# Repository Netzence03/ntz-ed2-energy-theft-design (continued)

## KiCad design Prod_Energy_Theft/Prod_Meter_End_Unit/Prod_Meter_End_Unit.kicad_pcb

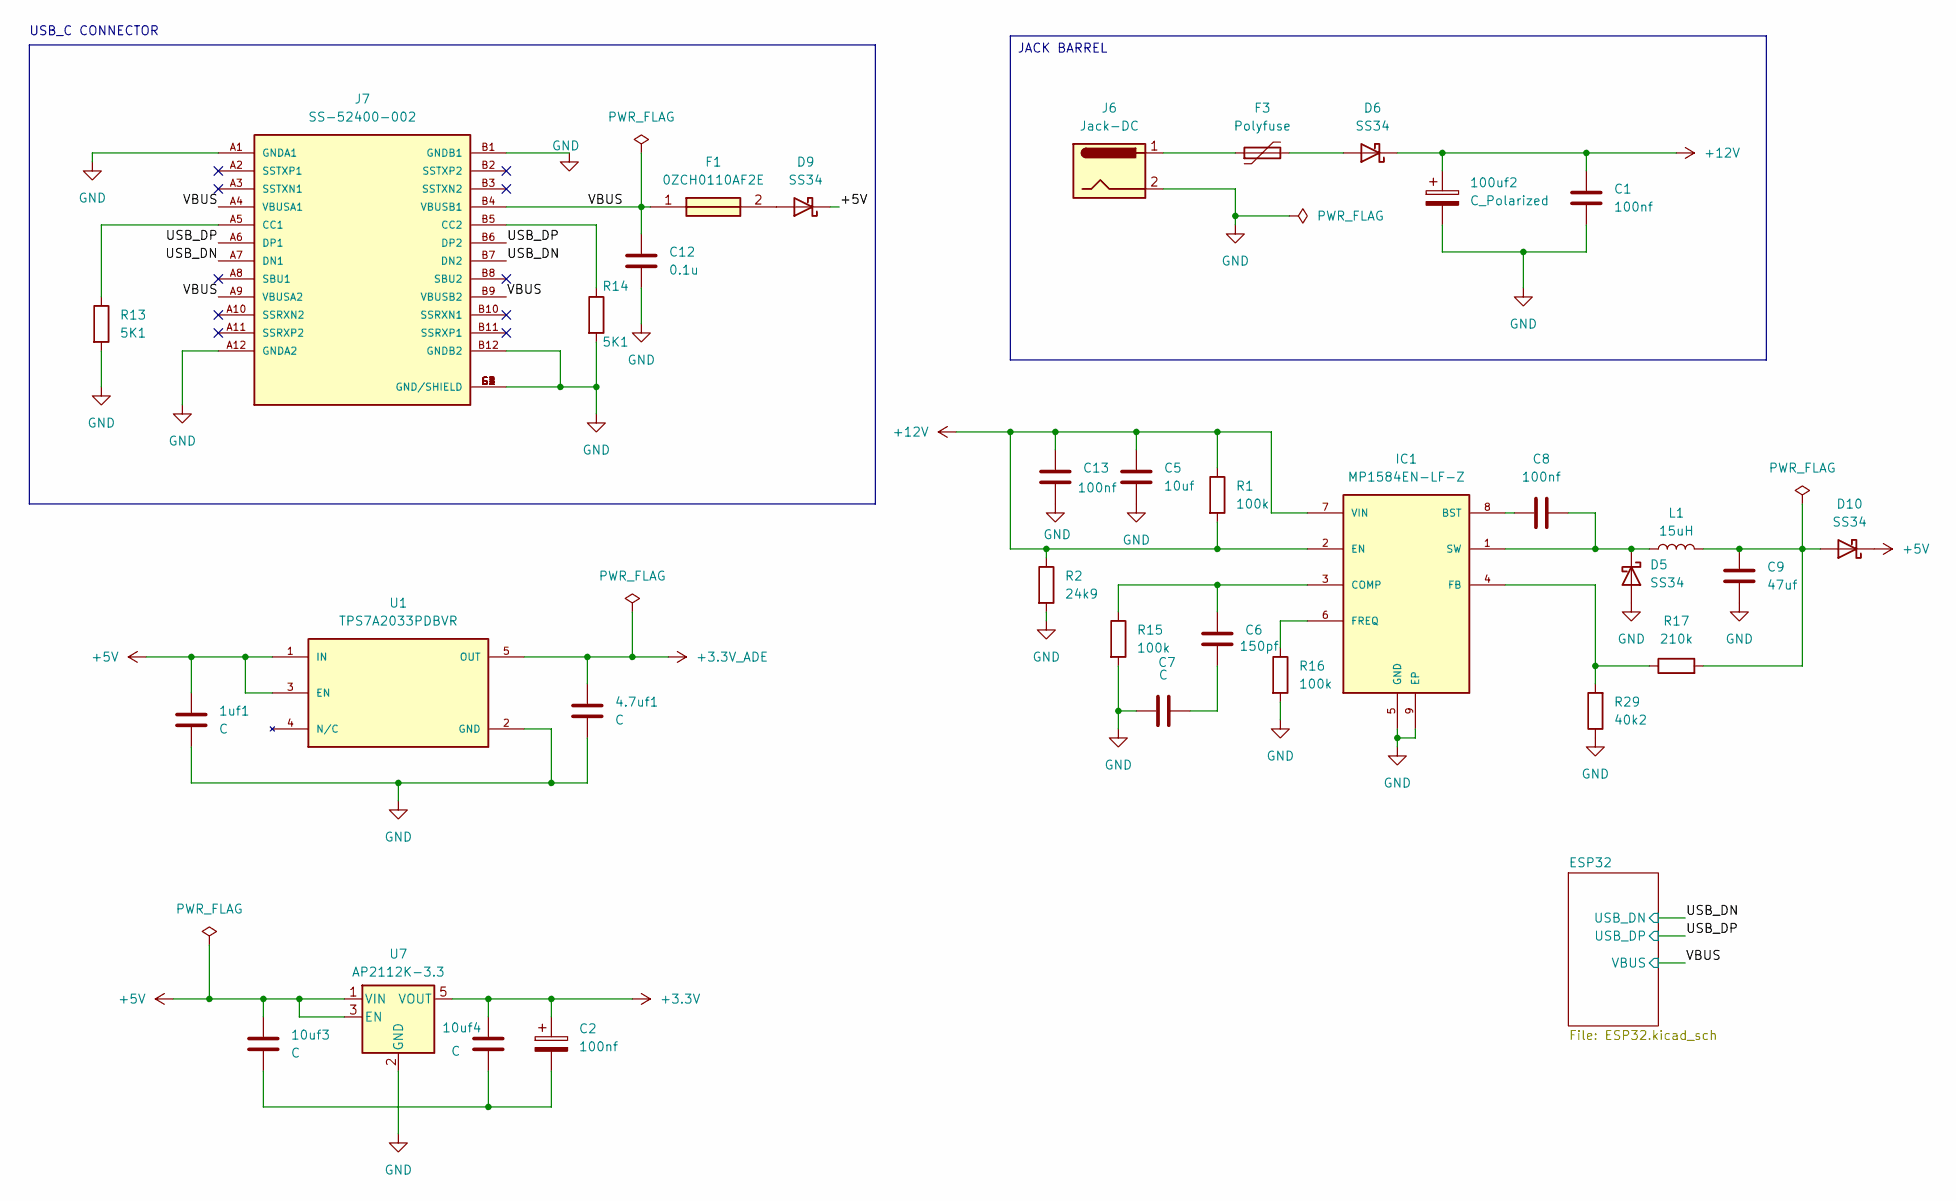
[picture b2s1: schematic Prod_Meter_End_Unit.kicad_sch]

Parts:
1uf1, 4.7uf1, 10uf3, 10uf4: C; C_0805_2012Metric
100uf2: C_Polarized; C_0805_2012Metric
C1, C2, C8, C13: 100nf; C_0805_2012Metric
C5: 10uf; C_0805_2012Metric
C6: 150pf; C_0805_2012Metric
C7: C; C_0805_2012Metric
C9: 47uf; C_0805_2012Metric; Voltage 16V; MPN GRM32ER71C476KE15
C12: 0.1u; C_0805_2012Metric
D5, D6, D9, D10: SS34; D_SMA
F1: 0ZCH0110AF2E; FUSC3226X100N; Manufacturer_Part_Number 0ZCH0110AF2E
F3: Polyfuse; Fuse_1206_3216Metric
IC1: MP1584EN-LF-Z; SOIC127P600X170-9N; MOUSER_PART_NUMBER 946-MP1584ENLFZ
J6: Jack-DC; BarrelJack_GCT_DCJ200-10-A_Horizontal
J7: SS-52400-002; BELFUSE_SS-52400-002; PARTREV A0
L1: 15uH; L_0805_2012Metric
R1, R15, R16: 100k; R_0805_2012Metric
R2: 24k9; R_0805_2012Metric
R13, R14: 5K1; R_0805_2012Metric
R17: 210k; R_0805_2012Metric
R29: 40k2; R_0805_2012Metric
U1: TPS7A2033PDBVR; SOT95P280X145-5N; PARTREV H
U7: AP2112K-3.3; SOT-23-5

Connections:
+3.3V: 10uf4.1, C2.1, U7.5 (VOUT); also elsewhere on the board
+3.3V_ADE: 4.7uf1.1, U1.5 (OUT); also elsewhere on the board
+5V: 1uf1.1, 10uf3.1, D9.1 (K), D10.1 (K), U1.1 (IN), U1.3 (EN), U7.1 (VIN), U7.3 (EN)
+12V: 100uf2.1, C1.1, C5.1, C13.1, D6.1 (K), IC1.2 (EN), IC1.7 (VIN), R1.1, R1.2, R2.1; also elsewhere on the board
/USB_DN: J7.A7 (DN1), J7.B7 (DN2); also elsewhere on the board
/USB_DP: J7.A6 (DP1), J7.B6 (DP2); also elsewhere on the board
/VBUS: C12.1, F1.1, J7.A4 (VBUSA1), J7.A9 (VBUSA2), J7.B4 (VBUSB1), J7.B9 (VBUSB2); also elsewhere on the board
GND: 1uf1.2, 4.7uf1.2, 100uf2.2, C1.2, C5.2, C7.1, C9.2, C12.2, C13.2, D5.2 (A), IC1.5 (GND), IC1.9 (EP), J6.2, J7.A1 (GNDA1), J7.A12 (GNDA2), J7.B1 (GNDB1), J7.B12 (GNDB2), J7.G1 (GND/SHIELD), J7.G2 (GND/SHIELD), J7.G3 (GND/SHIELD), J7.G4 (GND/SHIELD), J7.S1 (GND/SHIELD), J7.S2 (GND/SHIELD), J7.S3 (GND/SHIELD), J7.S4 (GND/SHIELD), R2.2, R13.2, R14.2, R15.2, R16.2, R29.1, U1.2 (GND), U7.2 (GND); also elsewhere on the board
unnamed: 10uf3.2, 10uf4.2, C2.2
unnamed: C6.2, C7.2
unnamed: C8.2, D5.1 (K), IC1.1 (SW), L1.1
unnamed: D6.2 (A), F3.2
unnamed: D9.2 (A), F1.2
unnamed: C9.1, D10.2 (A), L1.2, R17.2
unnamed: F3.1, J6.1
unnamed: C8.1, IC1.8 (BST)
unnamed: C6.1, IC1.3 (COMP), R15.1
unnamed: IC1.4 (FB), R17.1, R29.2
unnamed: IC1.6 (FREQ), R16.1
unnamed: J7.A5 (CC1), R13.1
unnamed: J7.B5 (CC2), R14.1

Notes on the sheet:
USB_C CONNECTOR
JACK BARREL

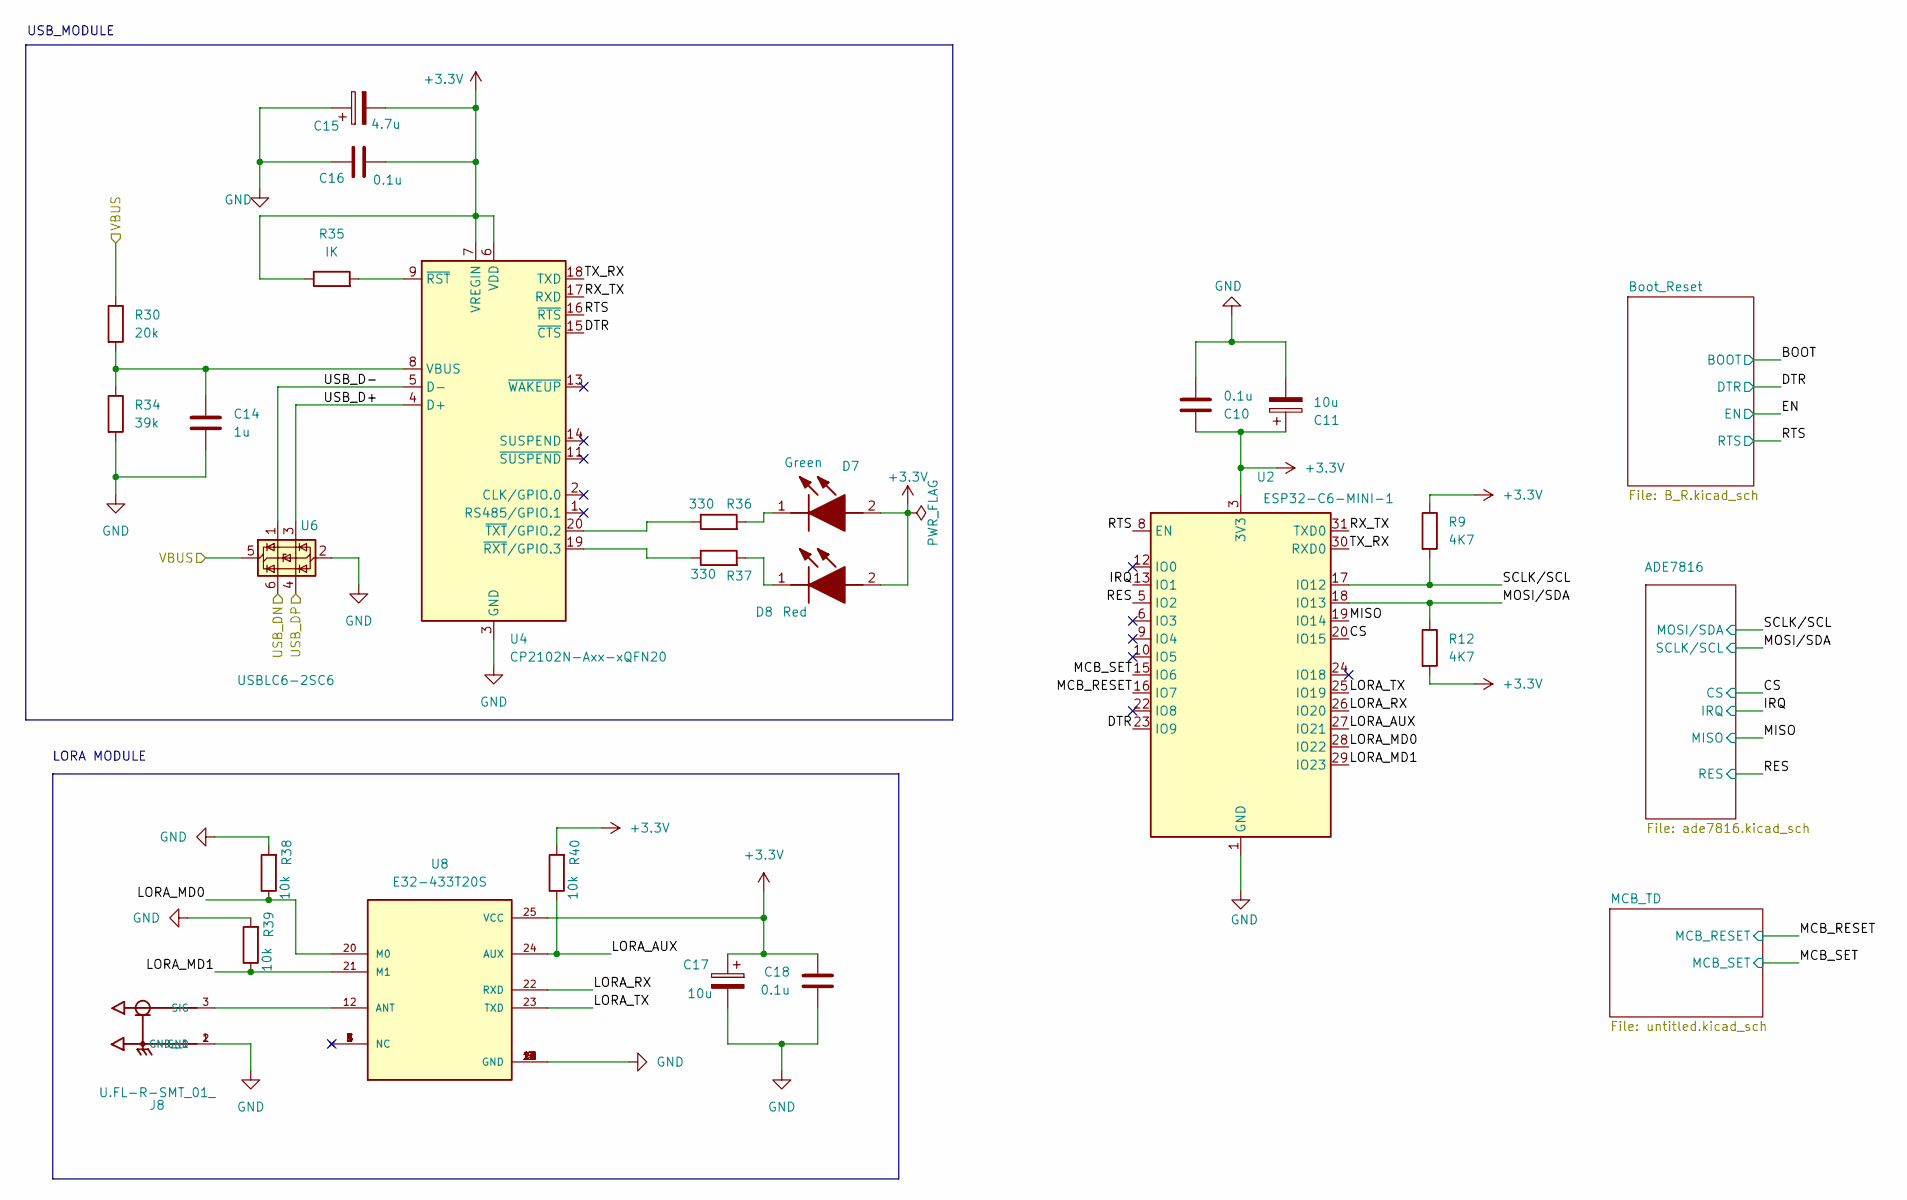
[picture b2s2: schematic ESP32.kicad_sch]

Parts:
C10, C16, C18: 0.1u; C_0805_2012Metric
C11, C17: 10u; C_0805_2012Metric
C14: 1u; C_0805_2012Metric
C15: 4.7u; C_0805_2012Metric
D7: Green; LEDC2012X120N; Manufacturer_Part_Number LTST-C170GKT; Mouser Part Number 859-LTST-C170GKT
D8: Red; LEDC2012X120N; Manufacturer_Part_Number LTST-C170KRKT; Mouser Part Number 859-LTST-C170KRKT
J8: U.FL-R-SMT_01_; HRS_U.FL-R-SMT_01_
R9, R12: 4K7; R_0805_2012Metric
R30: 20k; R_0805_2012Metric
R34: 39k; R_0805_2012Metric
R35: IK; R_0805_2012Metric
R36, R37: 330; R_0805_2012Metric
R38, R39, R40: 10k; R_0805_2012Metric
U2: ESP32-C6-MINI-1
U4: CP2102N-Axx-xQFN20; IC_CP2102N-A01-GQFN20
U6: USBLC6-2SC6; SOT-23-6
U8: E32-433T20S; MODULE_E32-433T20S; PARTREV 1.00

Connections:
+3.3V: C10.1, C11.1, C15.2, C16.2, C17.1, C18.1, D7.2 (A), D8.2 (A), R9.1, R12.2, R35.1, R40.2, U2.3 (3V3), U4.6 (VDD), U4.7 (VREGIN), U8.25 (VCC); also elsewhere on the board
/ESP32/CS: U2.20 (IO15); also elsewhere on the board
/ESP32/DTR: U2.23 (IO9), U4.15 (~CTS); also elsewhere on the board
/ESP32/IRQ: U2.13 (IO1); also elsewhere on the board
/ESP32/LORA_AUX: R40.1, U2.27 (IO21), U8.24 (AUX)
/ESP32/LORA_MD0: R38.1, U2.28 (IO22), U8.20 (M0)
/ESP32/LORA_MD1: R39.1, U2.29 (IO23), U8.21 (M1)
/ESP32/LORA_RX: U2.26 (IO20), U8.22 (RXD)
/ESP32/LORA_TX: U2.25 (IO19), U8.23 (TXD)
/ESP32/MCB_RESET: U2.16 (IO7); also elsewhere on the board
/ESP32/MCB_SET: U2.15 (IO6); also elsewhere on the board
/ESP32/MISO: U2.19 (IO14); also elsewhere on the board
/ESP32/MOSI/SDA: R12.1, U2.18 (IO13); also elsewhere on the board
/ESP32/RES: U2.5 (IO2); also elsewhere on the board
/ESP32/RTS: U2.8 (EN), U4.16 (~RTS); also elsewhere on the board
/ESP32/RX_TX: U2.31 (TXD0), U4.17 (RXD)
/ESP32/SCLK/SCL: R9.2, U2.17 (IO12); also elsewhere on the board
/ESP32/TX_RX: U2.30 (RXD0), U4.18 (TXD)
/ESP32/USB_D+: U4.4 (D+), U6.3 (I/O2)
/ESP32/USB_D-: U4.5 (D-), U6.1 (I/O1)
/USB_DN: U6.6 (I/O1); also elsewhere on the board
/USB_DP: U6.4 (I/O2); also elsewhere on the board
/VBUS: R30.1, U6.5 (VBUS); also elsewhere on the board
GND: C10.2, C11.2, C14.2, C15.1, C16.1, C17.2, C18.2, J8.1 (GND), J8.2 (GND__1), R34.2, R38.2, R39.2, U2.1 (GND), U2.2 (GND), U2.11 (GND), U2.14 (GND), U2.36 (GND), U2.37 (GND), U2.38 (GND), U2.39 (GND), U2.40 (GND), U2.41 (GND), U2.42 (GND), U2.43 (GND), U2.44 (GND), U2.45 (GND), U2.46 (GND), U2.47 (GND), U2.48 (GND), U2.49 (GND), U2.50 (GND), U2.51 (GND), U2.52 (GND), U2.53 (GND), U4.3 (GND), U4.12 (GND), U4.21 (GND), U6.2 (GND), U8.2 (GND), U8.8 (GND), U8.11 (GND), U8.13 (GND), U8.14 (GND), U8.15 (GND), U8.16 (GND), U8.19 (GND), U8.26 (GND); also elsewhere on the board
unnamed: D7.1 (K), R36.2
unnamed: D8.1 (K), R37.2
unnamed: J8.3 (SIG), U8.12 (ANT)
unnamed: C14.1, R30.2, R34.1, U4.8 (VBUS)
unnamed: R35.2, U4.9 (~RST)
unnamed: R37.1, U4.19 (~RXT/GPIO.3)
unnamed: R36.1, U4.20 (~TXT/GPIO.2)

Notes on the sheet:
LORA MODULE
USB_MODULE

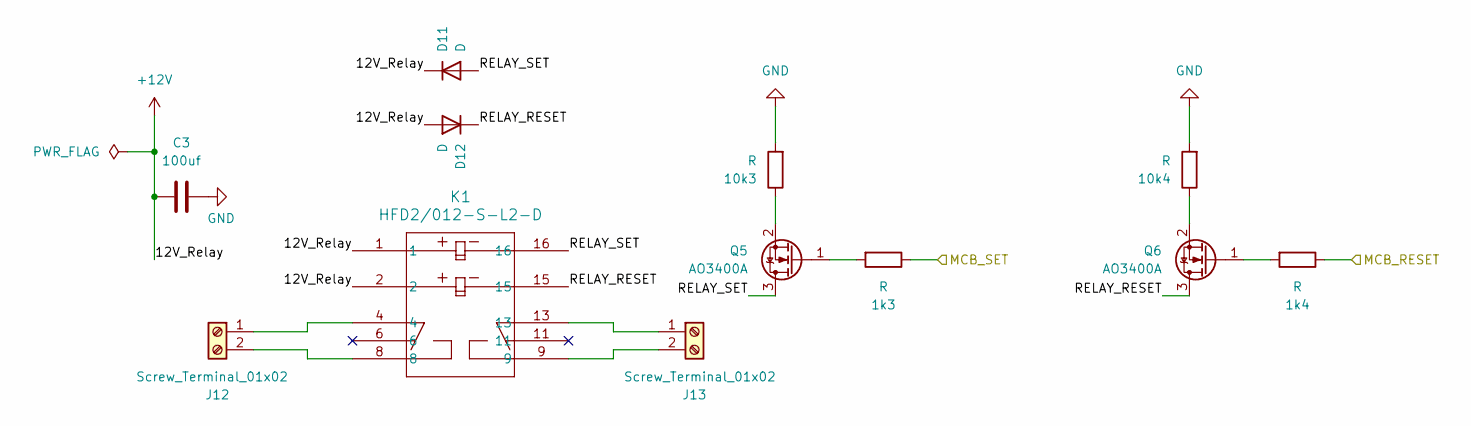
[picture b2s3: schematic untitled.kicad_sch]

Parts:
1k3, 1k4, 10k3, 10k4: R; R_0805_2012Metric
C3: 100uf; C_0805_2012Metric
D11, D12: D; D_SOD-123
J12, J13: Screw_Terminal_01x02; TerminalBlock_Phoenix_MKDS-1,5-2-5.08_1x02_P5.08mm_Horizont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
K1: HFD2/012-S-L2-D; RELAY10_HFD2&slash_012_HNG
Q5, Q6: AO3400A; SOT-23

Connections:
+12V: C3.1, D11.1 (K), D12.2 (A), K1.1, K1.2; also elsewhere on the board
/ESP32/MCB_RESET: 1k4.1; also elsewhere on the board
/ESP32/MCB_SET: 1k3.1; also elsewhere on the board
/ESP32/MCB_TD/RELAY_RESET: D12.1 (K), K1.15, Q6.3 (D)
/ESP32/MCB_TD/RELAY_SET: D11.2 (A), K1.16, Q5.3 (D)
GND: 10k3.2, 10k4.2, C3.2; also elsewhere on the board
unnamed: J12.1, K1.4
unnamed: J12.2, K1.8
unnamed: J13.1, K1.13
unnamed: J13.2, K1.9
unnamed: 1k3.2, Q5.1 (G)
unnamed: 10k3.1, Q5.2 (S)
unnamed: 1k4.2, Q6.1 (G)
unnamed: 10k4.1, Q6.2 (S)

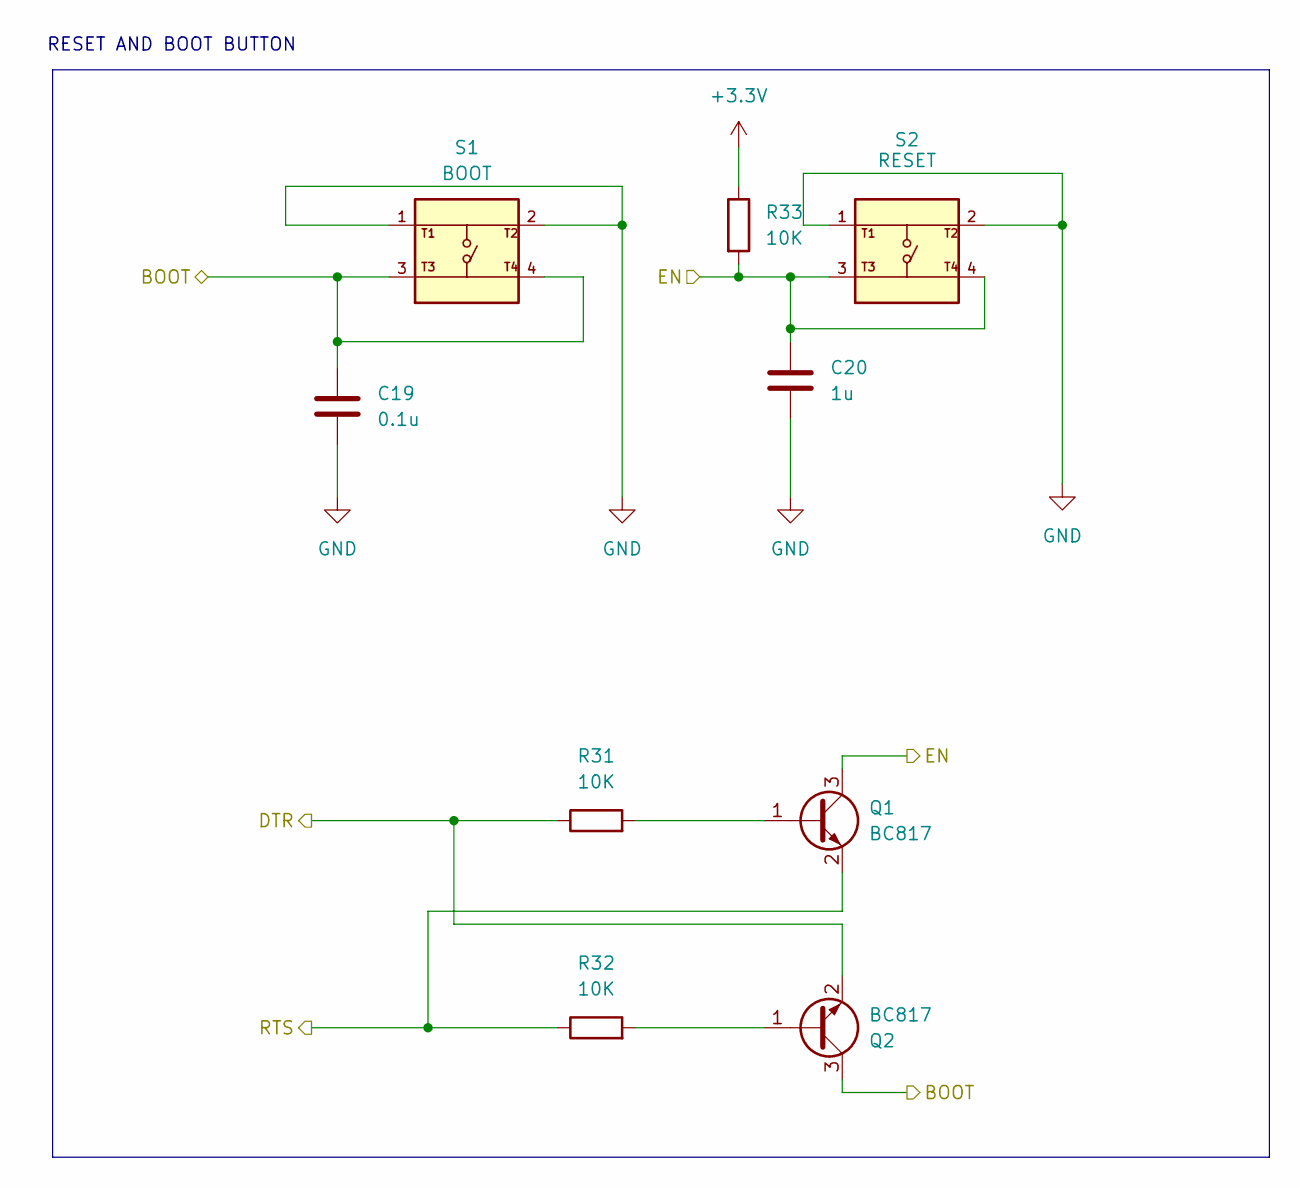
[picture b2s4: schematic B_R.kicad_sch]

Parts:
C19: 0.1u; C_0805_2012Metric
C20: 1u; C_0805_2012Metric
Q1, Q2: BC817; SOT-23
R31, R32, R33: 10K; R_0805_2012Metric
S1: BOOT; SW_USLPT2819DT2TR; PARTREV P
S2: RESET; SW_USLPT2819DT2TR; PARTREV P

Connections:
+3.3V: R33.1; also elsewhere on the board
/ESP32/BOOT: C19.1, Q2.3 (C), S1.3, S1.4
/ESP32/DTR: Q2.2 (E), R31.1; also elsewhere on the board
/ESP32/EN: C20.1, Q1.3 (C), R33.2, S2.3, S2.4
/ESP32/RTS: Q1.2 (E), R32.1; also elsewhere on the board
GND: C19.2, C20.2, S1.1, S1.2, S2.1, S2.2; also elsewhere on the board
unnamed: Q1.1 (B), R31.2
unnamed: Q2.1 (B), R32.2

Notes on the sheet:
RESET AND BOOT BUTTON

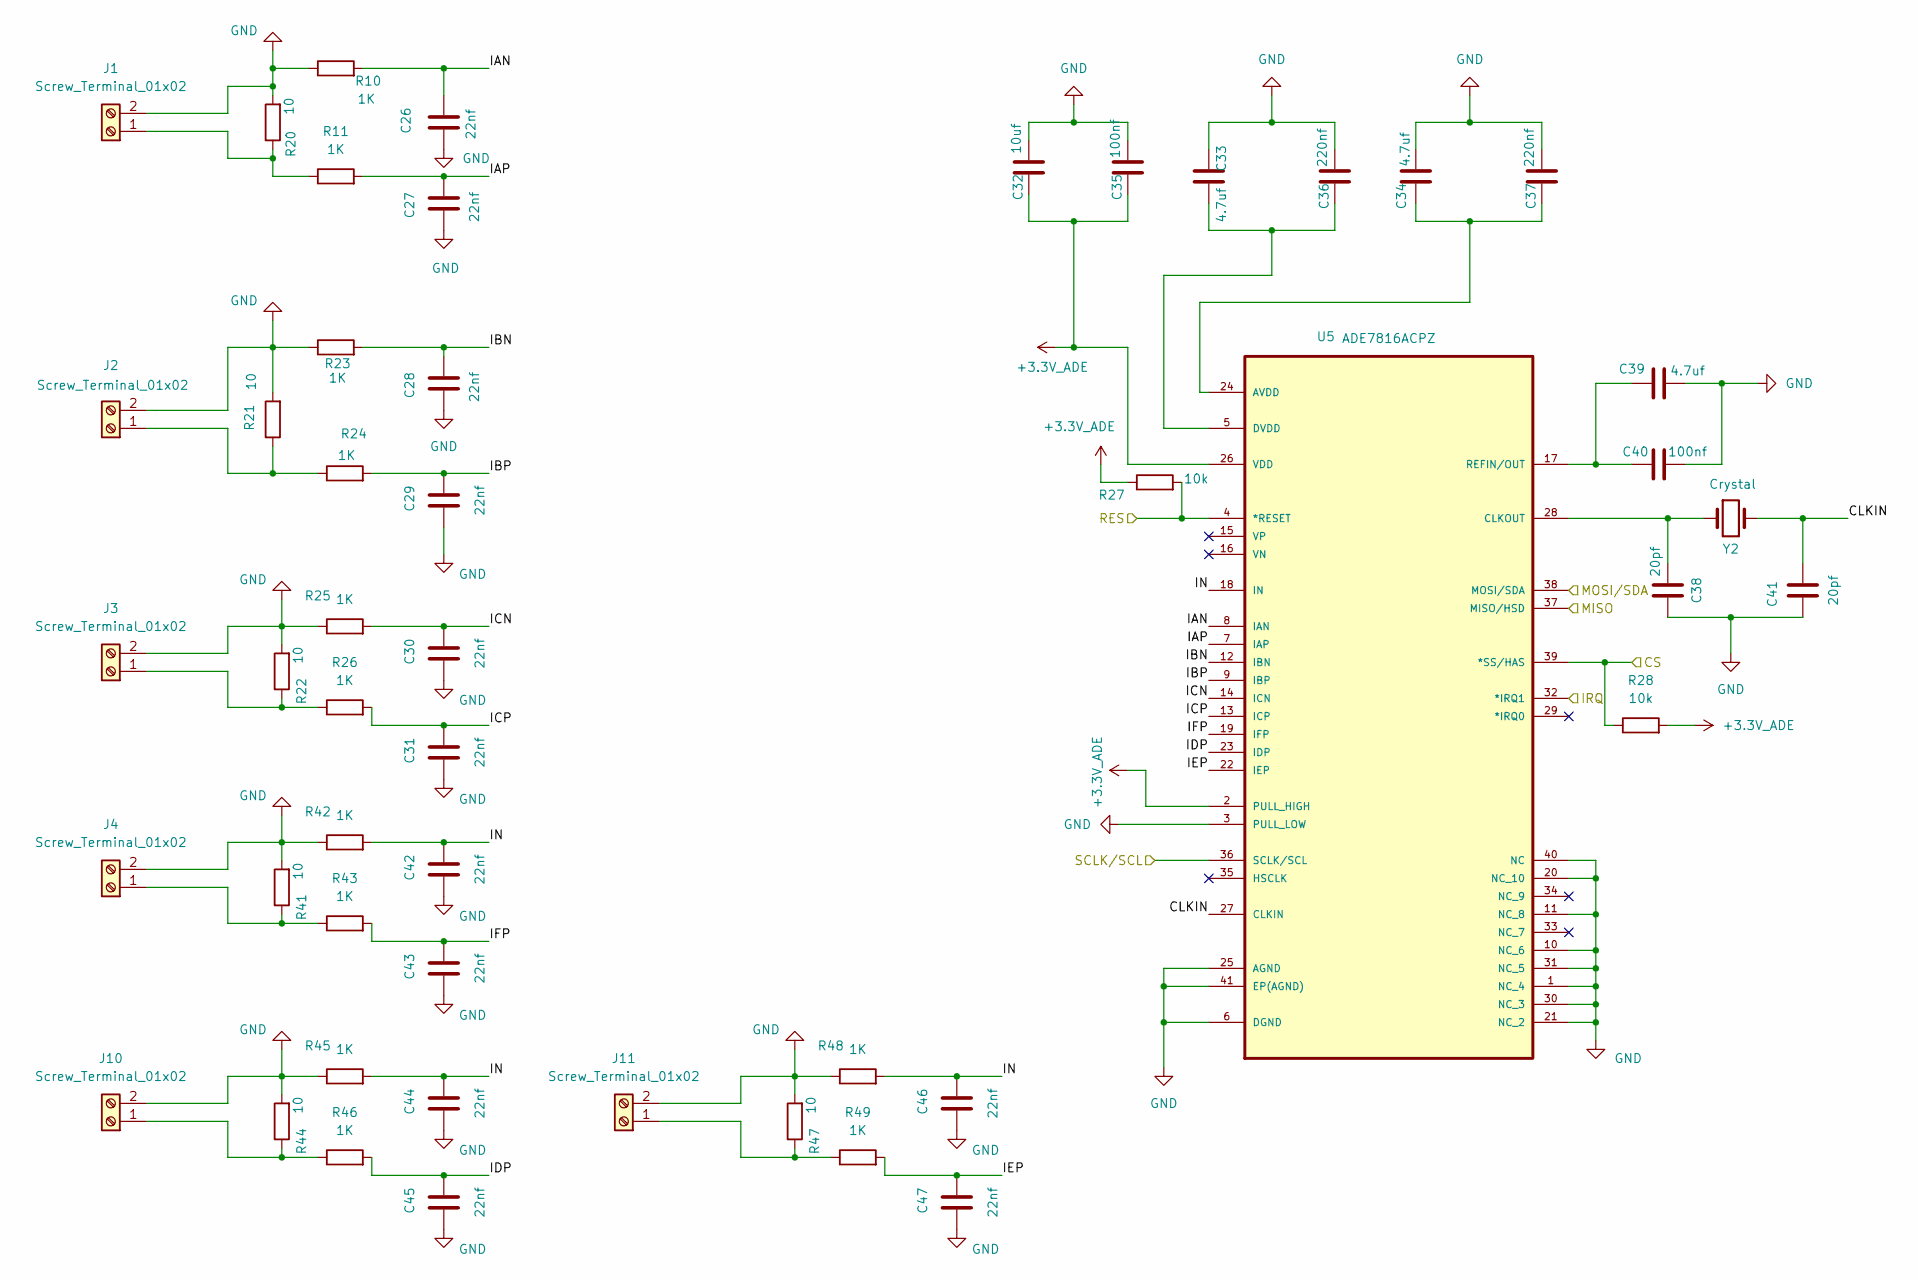
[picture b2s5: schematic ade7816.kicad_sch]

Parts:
C26, C27, C28, C29, C30, C31, C42, C43, C44, C45, C46, C47: 22nf; C_0805_2012Metric
C32: 10uf; C_0805_2012Metric
C33, C34, C39: 4.7uf; C_0805_2012Metric
C35, C40: 100nf; C_0805_2012Metric
C36, C37: 220nf; C_0805_2012Metric
C38, C41: 20pf; C_0805_2012Metric
J1, J2, J3, J4, J10, J11: Screw_Terminal_01x02; TerminalBlock_Phoenix_MKDS-1,5-2-5.08_1x02_P5.08mm_Horizont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
R10, R11, R23, R24, R25, R26, R42, R43, R45, R46, R48, R49: 1K; R_0805_2012Metric
R20, R21, R22, R41, R44, R47: 10; R_0805_2012Metric
R27, R28: 10k; R_0805_2012Metric
U5: ADE7816ACPZ; QFN50P600X600X80-41N; MPN ADE7816ACPZ
Y2: Crystal; Crystal_SMD_3225-4Pin_3.2x2.5mm

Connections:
+3.3V_ADE: C32.1, C35.1, R27.1, R28.2, U5.2 (PULL_HIGH), U5.26 (VDD); also elsewhere on the board
/ESP32/ADE7816/CLKIN: C41.2, U5.27 (CLKIN), Y2.2
/ESP32/ADE7816/IAN: C26.2, R10.2, U5.8 (IAN)
/ESP32/ADE7816/IAP: C27.2, R11.2, U5.7 (IAP)
/ESP32/ADE7816/IBN: C28.2, R23.2, U5.12 (IBN)
/ESP32/ADE7816/IBP: C29.2, R24.2, U5.9 (IBP)
/ESP32/ADE7816/ICN: C30.2, R25.2, U5.14 (ICN)
/ESP32/ADE7816/ICP: C31.2, R26.2, U5.13 (ICP)
/ESP32/ADE7816/IDP: C45.2, R46.2, U5.23 (IDP)
/ESP32/ADE7816/IEP: C47.2, R49.2, U5.22 (IEP)
/ESP32/ADE7816/IFP: C43.2, R43.2, U5.19 (IFP)
/ESP32/ADE7816/IN: C42.2, C44.2, C46.2, R42.2, R45.2, R48.2, U5.18 (IN)
/ESP32/CS: R28.1, U5.39 (*SS/HAS); also elsewhere on the board
/ESP32/IRQ: U5.32 (*IRQ1); also elsewhere on the board
/ESP32/MISO: U5.37 (MISO/HSD); also elsewhere on the board
/ESP32/MOSI/SDA: U5.36 (SCLK/SCL); also elsewhere on the board
/ESP32/RES: R27.2, U5.4 (*RESET); also elsewhere on the board
/ESP32/SCLK/SCL: U5.38 (MOSI/SDA); also elsewhere on the board
GND: C26.1, C27.1, C28.1, C29.1, C30.1, C31.1, C32.2, C33.1, C34.2, C35.2, C36.2, C37.2, C38.1, C39.2, C40.2, C41.1, C42.1, C43.1, C44.1, C45.1, C46.1, C47.1, J1.2, J2.2, J3.2, J4.2, J10.2, J11.2, R10.1, R20.2, R21.2, R22.2, R23.1, R25.1, R41.2, R42.1, R44.2, R45.1, R47.2, R48.1, U5.1 (NC_4), U5.3 (PULL_LOW), U5.6 (DGND), U5.10 (NC_6), U5.11 (NC_8), U5.20 (NC_10), U5.21 (NC_2), U5.25 (AGND), U5.30 (NC_3), U5.31 (NC_5), U5.40 (NC), U5.41 (EP(AGND)); also elsewhere on the board
unnamed: J1.1, R11.1, R20.1
unnamed: J2.1, R21.1, R24.1
unnamed: J3.1, R22.1, R26.1
unnamed: J4.1, R41.1, R43.1
unnamed: J10.1, R44.1, R46.1
unnamed: J11.1, R47.1, R49.1
unnamed: C34.1, C37.1, U5.24 (AVDD)
unnamed: C38.2, U5.28 (CLKOUT), Y2.1
unnamed: C33.2, C36.1, U5.5 (DVDD)
unnamed: C39.1, C40.1, U5.17 (REFIN/OUT)

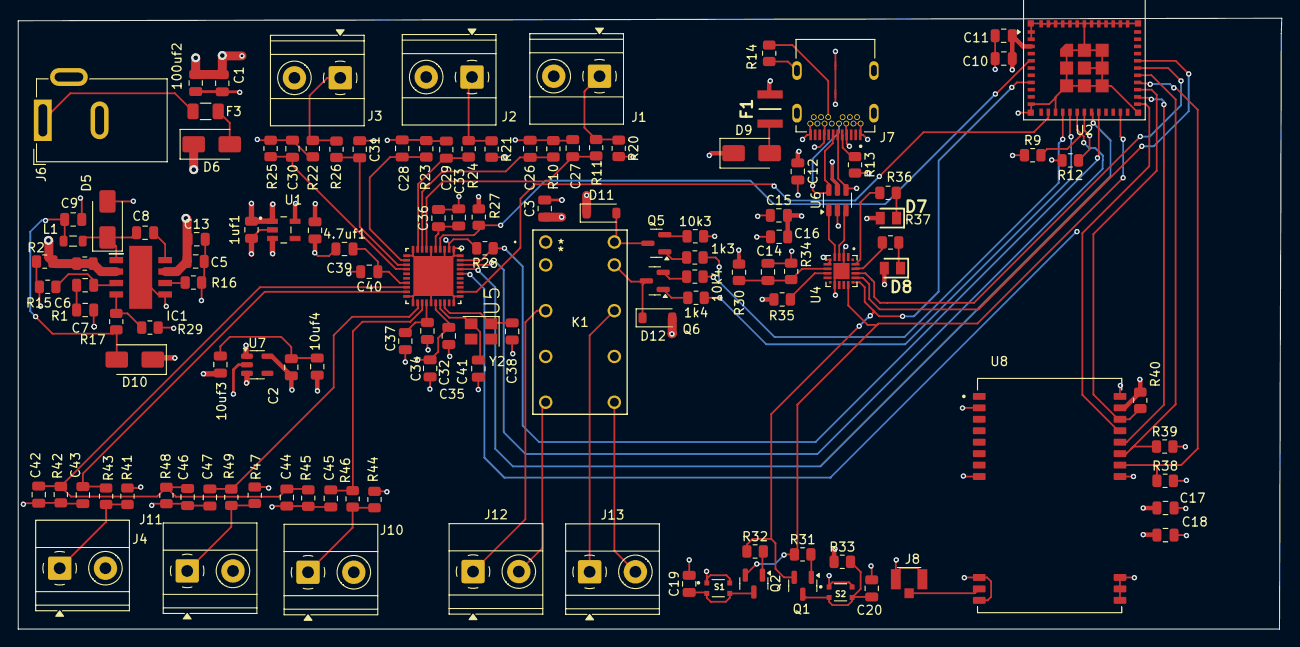
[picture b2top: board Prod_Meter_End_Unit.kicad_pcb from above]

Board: 4 copper layers, 140.2 x 67.8 mm, 129 parts (0 on the bottom side), 82 nets.

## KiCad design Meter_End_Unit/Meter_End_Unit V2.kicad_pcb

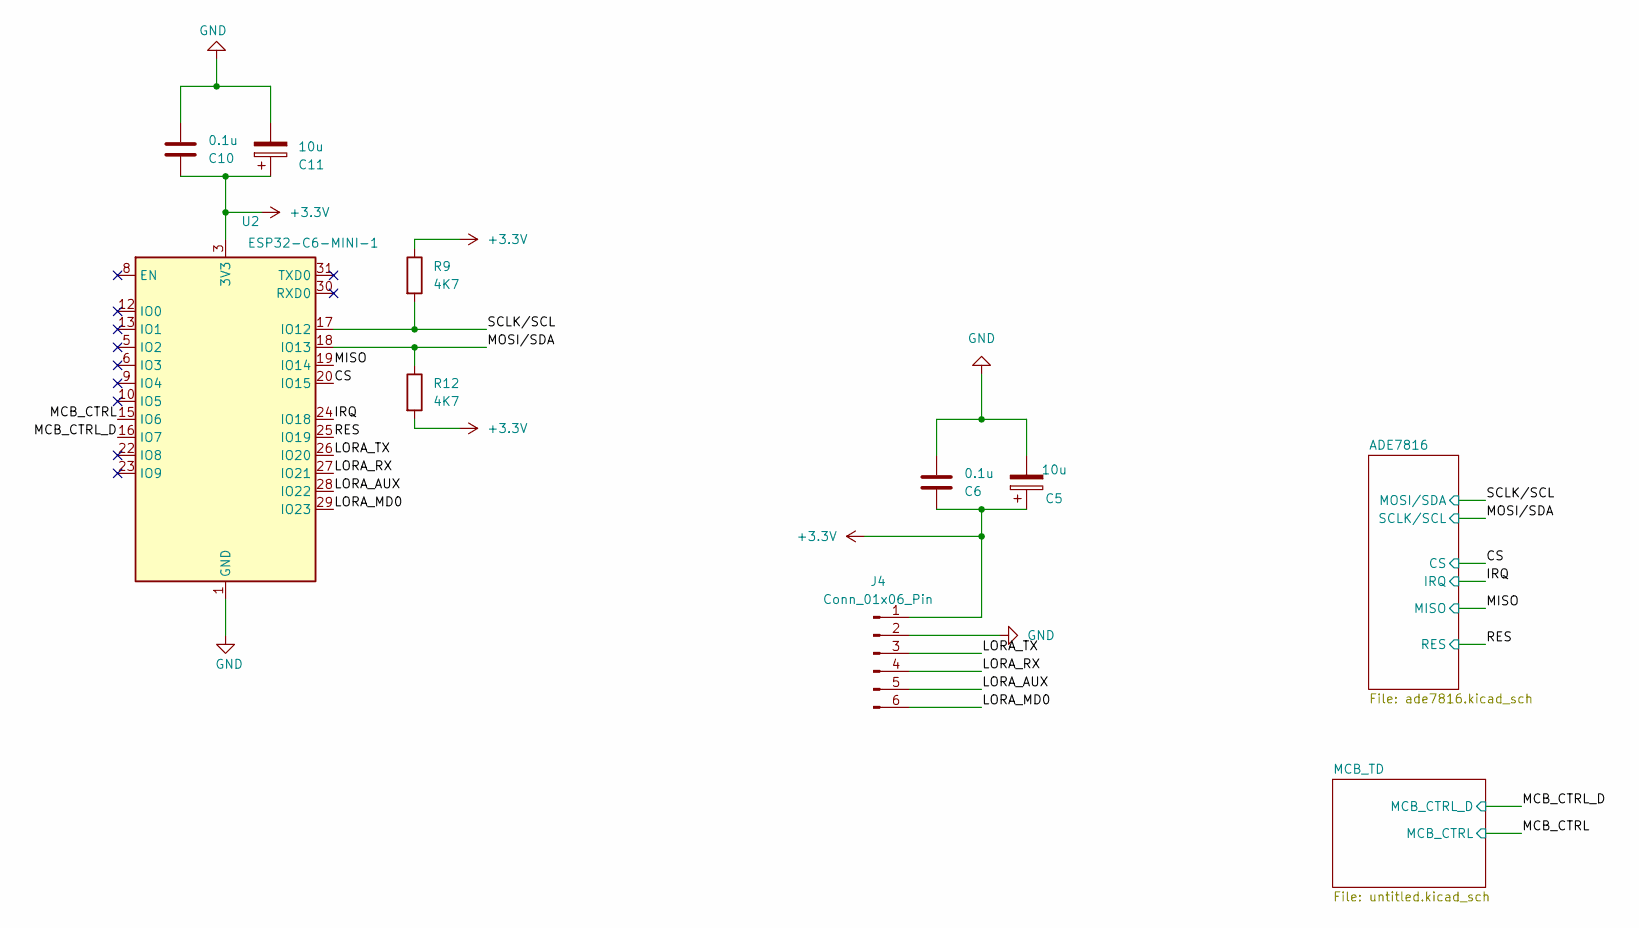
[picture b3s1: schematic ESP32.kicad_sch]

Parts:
C5, C11: 10u; C_0805_2012Metric
C6, C10: 0.1u; C_0805_2012Metric
J4: Conn_01x06_Pin; PinSocket_1x06_P2.54mm_Vertical
R9, R12: 4K7; R_0805_2012Metric
U2: ESP32-C6-MINI-1

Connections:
+3.3V: C5.1, C6.1, C10.1, C11.1, J4.1, R9.1, R12.2, U2.3 (3V3); also elsewhere on the board
/ESP32/CS: U2.20 (IO15); also elsewhere on the board
/ESP32/IRQ: U2.24 (IO18); also elsewhere on the board
/ESP32/LORA_AUX: J4.5, U2.28 (IO22)
/ESP32/LORA_MD0: J4.6, U2.29 (IO23)
/ESP32/LORA_RX: J4.4, U2.27 (IO21)
/ESP32/LORA_TX: J4.3, U2.26 (IO20)
/ESP32/MCB_CTRL: U2.15 (IO6); also elsewhere on the board
/ESP32/MCB_CTRL_D: U2.16 (IO7); also elsewhere on the board
/ESP32/MISO: U2.19 (IO14); also elsewhere on the board
/ESP32/MOSI/SDA: R12.1, U2.18 (IO13); also elsewhere on the board
/ESP32/RES: U2.25 (IO19); also elsewhere on the board
/ESP32/SCLK/SCL: R9.2, U2.17 (IO12); also elsewhere on the board
GND: C5.2, C6.2, C10.2, C11.2, J4.2, U2.1 (GND), U2.2 (GND), U2.11 (GND), U2.14 (GND), U2.36 (GND), U2.37 (GND), U2.38 (GND), U2.39 (GND), U2.40 (GND), U2.41 (GND), U2.42 (GND), U2.43 (GND), U2.44 (GND), U2.45 (GND), U2.46 (GND), U2.47 (GND), U2.48 (GND), U2.49 (GND), U2.50 (GND), U2.51 (GND), U2.52 (GND), U2.53 (GND); also elsewhere on the board

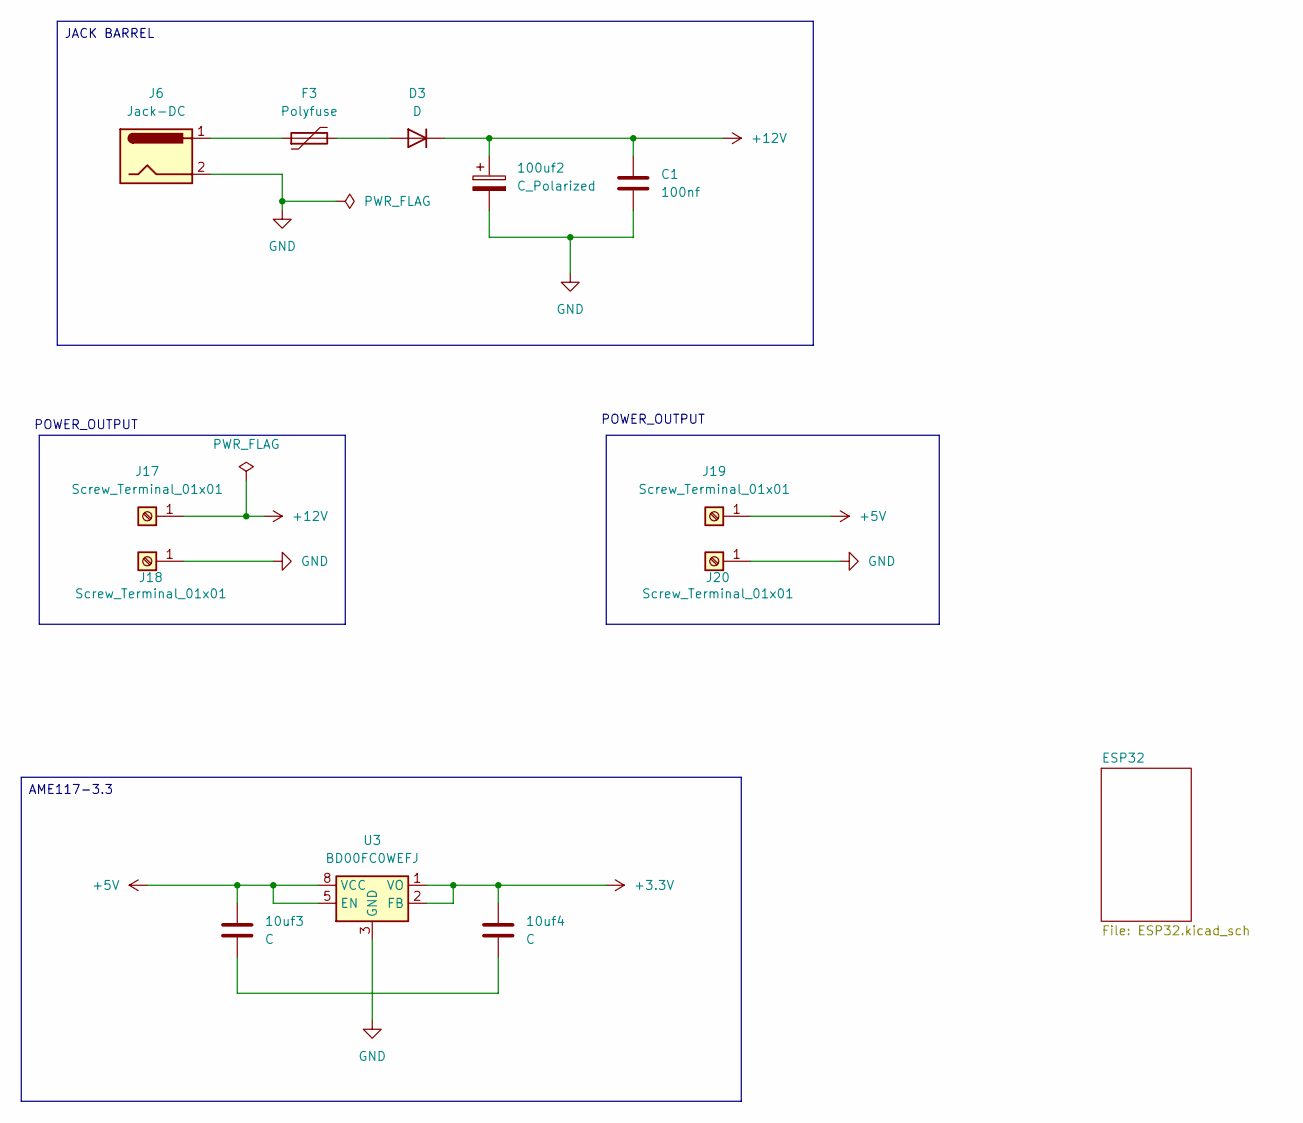
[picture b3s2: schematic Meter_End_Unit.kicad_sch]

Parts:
10uf3, 10uf4: C; C_0805_2012Metric
100uf2: C_Polarized; C_0805_2012Metric
C1: 100nf; C_0805_2012Metric
D3: D; D_SOD-123
F3: Polyfuse; Fuse_1206_3216Metric
J6: Jack-DC; BarrelJack_GCT_DCJ200-10-A_Horizontal
J17, J18, J19, J20: Screw_Terminal_01x01; TerminalBlock_1x01_P5.08mm
U3: BD00FC0WEFJ; HTSOP-8-1EP_3.9x4.9mm_P1.27mm_EP2.4x3.2mm

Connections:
+3.3V: 10uf4.1, U3.1 (VO), U3.2 (FB); also elsewhere on the board
+5V: 10uf3.1, J19.1, U3.5 (EN), U3.8 (VCC); also elsewhere on the board
+12V: 100uf2.1, C1.1, D3.1 (K), J17.1
GND: 100uf2.2, C1.2, J6.2, J18.1, J20.1, U3.3 (GND), U3.9 (GND); also elsewhere on the board
unnamed: 10uf3.2, 10uf4.2
unnamed: D3.2 (A), F3.2
unnamed: F3.1, J6.1

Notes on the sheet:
POWER_OUTPUT
JACK BARREL
AME117-3.3
